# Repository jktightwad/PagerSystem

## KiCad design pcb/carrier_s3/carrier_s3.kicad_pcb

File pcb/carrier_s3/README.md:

# Pager carrier board (ESP32-S3 SuperMini) — draft

**Status: laid out and routed (24 x 60.4 mm rectangle, 2 layers), DRC clean. Not ordered,
not tested. SuperMini row spacing and B+/B− pad position are still unmeasured.**

| Top | Bottom (seen from below) |
|---|---|
|  |  |

## Files and how to rebuild
- `design.py`: parts and every connection (single source for schematic and board).
- `schematic.py` → `schematic.svg` / `schematic.png`.
- `build_pcb.py`: outline, footprints, placement, nets → `carrier_s3.kicad_pcb`.
- `route_pcb.py`: scripted grid router (Freerouting was not available), GND pours
  on both layers, writes `drc_report.txt`. Needs numpy + scipy.
- `export_fab.sh`: Gerbers + drill → `fab/carrier_s3_gerbers.zip`, plus
  `fab/bom_jlc.csv` and `fab/cpl_jlc.csv` for JLCPCB assembly.
- `render.sh`: `pcb_top.png` / `pcb_bottom.png` (needs node + playwright).

```
python3 build_pcb.py && python3 route_pcb.py && sh export_fab.sh && sh render.sh
```
Open `carrier_s3.kicad_pcb` in KiCad 7+ to inspect or edit by hand.

## Board notes
- Rules: 0.2 mm clearance, 0.25 mm signal / 0.3–0.5 mm power tracks,
  0.6/0.3 mm vias, 0.3 mm to the edge; within standard JLCPCB/PCBWay limits.
- Plain rectangle, as wide as the SuperMini (24 mm). The SuperMini lies
  sideways along the top: USB-C end flush with the left edge (plug not
  blocked), antenna end flush with the right edge. No copper (pour, tracks, vias) on
  either layer under the antenna end (`ANT_LEN` = 5 mm, an estimate: measure)
  or in the corner just below it. All pins are on the board.
- Soldered flat by its castellated edges onto long pads (tolerate about
  ±1.5 mm of row-spacing error). No top copper under the middle of its body;
  a 2 mm strip inside each pad row is used to get the pins out.
- Its B+/B− pads are underneath: wires go down through the slot to the B+/B−
  holes (J6).
- Unused pins (TX, RX, GP3, GP6–GP11) each go to a 0.9 mm solder hole at the
  board edge, labelled on the bottom.
- Connectors: JST-PH 2.0 vertical, all the same way round: GND on the left
  pin (square pad), power on the right, signal in the middle. Labelled on
  the top: `BAT - +`, `DOCK - +`, `MOTOR - +`, `RING G D V`, `TOUCH G O V`. Their
  holes also take wires directly. J1 battery: + is the RIGHT pin (pin 2,
  round pad), ground the left (square pad), to match the battery plug with
  its tab facing the top of the board. **Check against your battery plug before soldering a
  connector** — the latch makes it one-way.
- Buzzer (9 mm, 5 mm pin spacing) on the board, hand-soldered. Power switch:
  two wire holes (the switch stays in its mount in the base). Buzzer and motor
  are on GP12 / GP13 (away from the antenna end).
- 4 × M2 holes (2.2 mm) in the corners, 2.1 mm from both edges, copper kept
  2 mm from centre for the screw head. Strips above the SuperMini and below
  the connectors make room for them. The top-right one is near the antenna
  end (about 4 mm); no copper round it.
- Not fitted (pads kept, the hand-wired prototype works without them):
  C1/C2 (100 nF divider filters, 0603) and C3 (47 uF ring bulk cap, 1206,
  e.g. C96123: hand-solder it if the ring flickers or resets the board at
  high brightness).
- Assembled parts kept to 4 types to cut JLCPCB's per-part loading fee:
  100k, 330R (ring data and both MOSFET gates), AO3400A, B5819W.
- JLCPCB assembly: top side only, all basic parts (LCSC numbers checked on
  lcsc.com / jlcpcb.com, Nov 2026). Check part rotations in JLC's placement
  preview before paying.

## Circuit
- Battery (J1) → power switch SW1 → **VBAT**: SuperMini B+ (short wire up
  through the board), LED ring, buzzer, motor, battery divider.
- Pogo (J5, from the pogo tower) **5 V** → SuperMini 5V pin (its charger
  charges the battery) and the dock divider.
- SuperMini **3V3** → touch module only.
- Buzzer and motor: low-side AO3400A MOSFETs, 330 Ω gate resistor, 100 kΩ
  pull-down; Schottky across the motor.
- Pins: dock GP1, battery GP2, touch GP4, ring GP5, buzzer GP12, motor GP13.
  (Firmware: the S3 build must use these; the LOLIN build keeps its own pins.)

## Still to confirm before ordering
1. SuperMini: row-to-row spacing, B+/B− pad position, and how far the antenna
   reaches in from its end (`ANT_LEN`).
2. Battery plug polarity against J1.
3. Hole positions against the Rev 2 base columns (enclosure not yet changed).

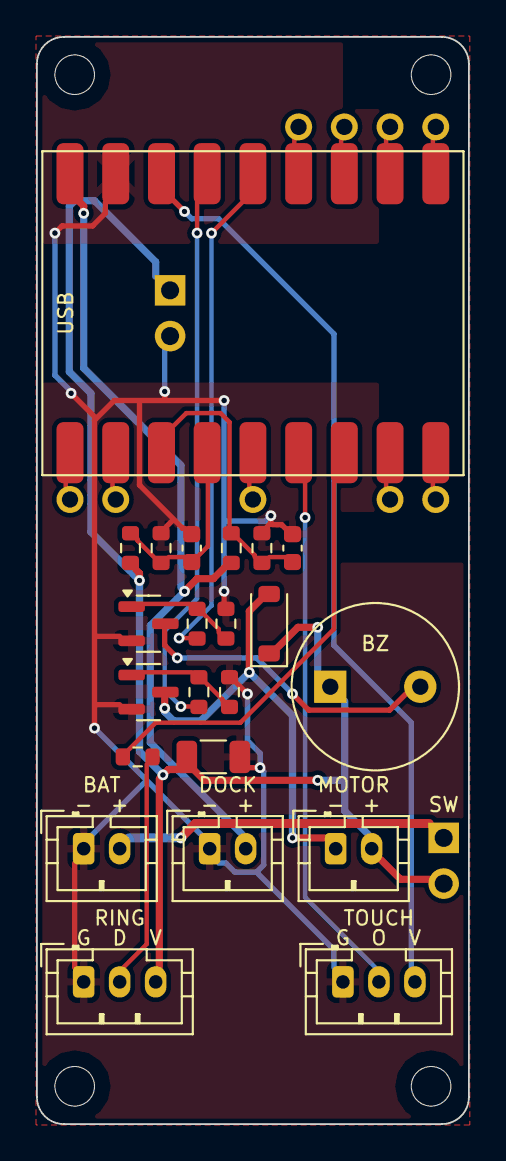
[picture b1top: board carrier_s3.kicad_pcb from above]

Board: 2 copper layers, 24.0 x 60.4 mm, 29 parts (0 on the bottom side), 16 nets.

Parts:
BZ1: Buzzer 9 mm
C1, C2: 100nF; C_0603_1608Metric
C3: 47uF 10V; C_1206_3216Metric
D1: B5819W; D_SOD-123
H1: B+/B- wires
J1: Battery; JST_PH_B2B-PH-K_1x02_P2.00mm_Vertical
J2: LED ring; JST_PH_B3B-PH-K_1x03_P2.00mm_Vertical
J3: Motor; JST_PH_B2B-PH-K_1x02_P2.00mm_Vertical
J4: Touch; JST_PH_B3B-PH-K_1x03_P2.00mm_Vertical
J5: Pogo (tower); JST_PH_B2B-PH-K_1x02_P2.00mm_Vertical
J6: SuperMini B+/B-
MH1, MH2, MH3, MH4: M2; MountingHole_2.2mm_M2
Q1, Q2: AO3400A; SOT-23
R1, R3, R5: 330R; R_0603_1608Metric
R2, R4, R6, R7, R8, R9: 100k; R_0603_1608Metric
SW1: Switch
U1: ESP32-S3 SuperMini

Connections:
3V3: J4.3, U1.3V3
BAT+: J1.2, SW1.1
BAT_SENSE: C1.1, R6.2, R7.1, U1.GP2
BUZ_-: BZ1.2, Q1.3
BUZ_G: Q1.1, R1.2, R2.1
BUZ_IO: R1.1, U1.GP12
DOCK_SENSE: C2.1, R8.2, R9.1, U1.GP1
GND: C1.2, C2.2, C3.2, J1.1, J2.1, J4.1, J5.1, J6.2, Q1.2, Q2.2, R2.2, R4.2, R7.2, R9.2, U1.GND
MOT_-: D1.2, J3.1, Q2.3
MOT_G: Q2.1, R3.2, R4.1
MOT_IO: R3.1, U1.GP13
POGO5V: J5.2, R8.1, U1.5V
RING_DATA: J2.2, R5.2
RING_IO: R5.1, U1.GP5
TOUCH: J4.2, U1.GP4
VBAT: BZ1.1, C3.1, D1.1, J2.3, J3.2, J6.1, R6.1, SW1.2

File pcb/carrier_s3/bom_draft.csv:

Qty,Refs,Value,Footprint,LCSC (verify),Notes
1,U1,ESP32-S3 SuperMini,SUPERMINI,,hand-soldered; B+/B- wired through the slot to J6
1,SW1,Slide switch,SWITCH,,power: breaks battery +; wired to two pads
1,BZ1,9 mm buzzer (TDB05),BUZZER,,on the board; 5 mm pin spacing; hand-soldered
2,Q1 Q2,AO3400A,SOT-23,C20917,
3,R1 R3 R5,330R,0603,C23138,MOSFET gates + ring data
6,R2 R4 R6 R7 R8 R9,100k,0603,C25803,
2,C1 C2,100nF,0603,(C14663),NOT FITTED - optional divider filters
1,C3,47uF 10V,1206,(C96123),NOT FITTED - optional ring bulk cap
1,D1,B5819W,SOD-123,C8598,motor flyback
1,J1,Battery,PH2,,"JST-PH 2: GND, + (right)"
1,J2,LED ring,PH3,,"JST-PH 3: GND, DATA, VBAT"
1,J3,Motor,PH2,,"JST-PH 2: motor -, +"
1,J4,Touch,PH3,,"JST-PH 3: GND, OUT, 3V3"
1,J5,Pogo (tower),PH2,,"JST-PH 2: GND, 5V"
